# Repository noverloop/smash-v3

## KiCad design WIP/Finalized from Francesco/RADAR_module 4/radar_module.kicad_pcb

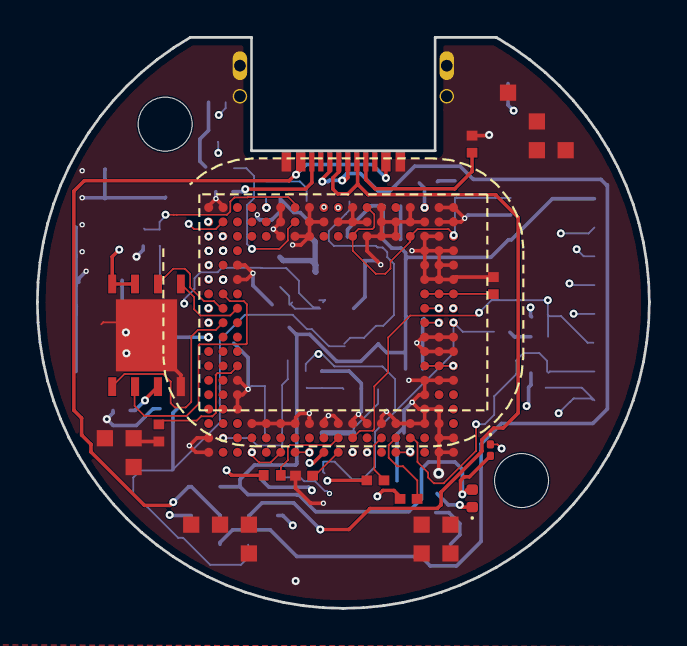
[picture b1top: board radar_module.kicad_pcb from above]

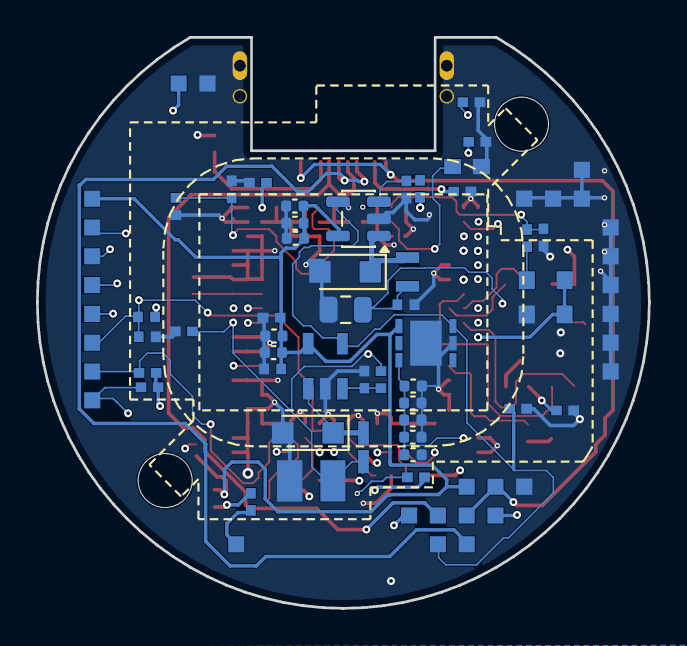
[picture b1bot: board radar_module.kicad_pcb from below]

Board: 20 copper layers, 34.0 x 31.7 mm, 59 parts (46 on the bottom side), 43 nets.

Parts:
C_AWR_1V2_1: T491T 22uF (3528-12 thinnest variant); C_0805_2012Metric
C_AWR_1V2_2, C_AWR_1V3_2, C_AWR_1V8_2, C_AWR_14APLL, C_AWR_14SYNTH: C0402 X7R 100nF; C_0402_1005Metric
C_AWR_1V3_1: T491T 22uF (3528-12 thinnest variant); CP_EIA-3528-12_Kemet-T
C_AWR_1V8_1_1, C_AWR_1V8_1_2, C_AWR_1V8_1_3, C_AWR_1V8_1_4, C_AWR_1V8_1_5: C-Series MIL-PRF-32535 X7R 0603 2.2uF; C_0402_1005Metric
C_AWR_BUCK_IN1_1, C_AWR_BUCK_IN1_2, C_AWR_BUCK_IN1_3, C_AWR_BUCK_IN1_4, C_AWR_BUCK_IN1_5: C-Series MIL-PRF-32535 X7R 0603 2.2uF; C_0402_1005Metric
C_AWR_BUCK_IN2: C0402 X7R 100nF; C_0402_1005Metric
C_AWR_CLKM: SQCSVA 100pF; C_0603_1608Metric
C_AWR_FLASH_VCC: C0402 X7R 100nF; C_0402_1005Metric
C_AWR_NRST: C0402 X7R 100nF; C_0402_1005Metric
C_AWR_OSC_VDD: C0402 X7R 100nF; C_0402_1005Metric
C_AWR_VBGAP: C0402 X7R 100nF; C_0402_1005Metric
C_AWR_VOUT_PA: C0402 X7R 100nF; C_0402_1005Metric
C_NOSE_LED: C0402 X7R 100nF; C_0402_1005Metric
D_AWR_BUCK12, D_AWR_BUCK13: MBRS340T3G; Nexperia_CFP3_SOD-123W
D_NOSE_G: LTST-C190GKT; LED_0402_1005Metric
D_NOSE_R: LTST-C190KRKT; LED_0201_0603Metric
J_USB_C: UJ20-C-H-G-MSMT-1A-P16-TR-67; SAMESKY_UJ20-C-H-G-MSMT-1A-P16-TR-67
J_radar_module_spacer_radar_module_nose_cap: LGA_lands; J_radar_module_spacer_radar_module_nose_cap
L_AWR_BUCK12, L_AWR_BUCK13: TMS201210ALM-2R2MTAA; L_2012_2.0x1.25mm
P_radar_module_spacer_companion_compute_radar_module: LGA_lands; P_radar_module_spacer_companion_compute_radar_module
R_AWR12_FB1, R_AWR12_FB2, R_AWR13_FB2: CRCW0402 100k 1% e3; R_0402_1005Metric
R_AWR13_FB1: CRCW0402 118k 1% e3; R_0402_1005Metric
R_AWR_CLK_SER: CRCW0402 330 1% e3; R_0402_1005Metric
R_AWR_CLK_SH: CRCW0402 390 1% e3; R_0402_1005Metric
R_AWR_DRDY_PU: CRCW0402 10k 1% e3; R_0402_1005Metric
R_AWR_FAULT_PU: CRCW0402 100k 1% e3; R_0402_1005Metric
R_AWR_NERRIN_PU: CRCW0402 10k 1% e3; R_0402_1005Metric
R_AWR_NRST: CRCW0402 10k 1% e3; R_0402_1005Metric
R_AWR_SOP0, R_AWR_SOP1, R_AWR_SOP2: CRCW0402 10k 1% e3; R_0402_1005Metric
R_AWR_WARMRST_PU: CRCW0402 10k 1% e3; R_0402_1005Metric
R_NOSE_LED_G: CRCW0402 330 1% e3; R_0402_1005Metric
R_NOSE_LED_R: CRCW0402 330 1% e3; R_0402_1005Metric
R_RADAR_EN_PD: CRCW0402 100k 1% e3; R_0402_1005Metric
R_USB_CC1, R_USB_CC2: CRCW0402 5.1k 1% e3; R_0402_1005Metric
U_AWR: AWR1843ARBGALPQ1; BGA180C80P18X18_1500X1500X96
U_AWR_BUCK12: LMR10510XMFE/NOPB; SOT-23-5
U_AWR_BUCK13: LMR10510XMFE/NOPB; SOT95P280X145-5N
U_AWR_FLASH: SST26VF080A-104I/MF; SON127P600X500X80-9N-D
U_AWR_LDO18: LDL112PV18R; SON95P300X300X100-7N-D
Y_AWR_HSE: DSC1001CI5-040.0000; DSC1001CI50080000

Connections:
AWR_1V2: C_AWR_1V2_1.1, C_AWR_1V2_2.1, L_AWR_BUCK12.2, R_AWR12_FB1.1, U_AWR.A5, U_AWR.C1, U_AWR.E1, U_AWR.J1, U_AWR.V4, U_AWR.V6, U_AWR.V7, U_AWR.V8, U_AWR.V12, U_AWR.V14, U_AWR.V15
AWR_1V2_FB: R_AWR12_FB1.2, R_AWR12_FB2.1, U_AWR_BUCK12.3
AWR_1V2_SW: D_AWR_BUCK12.1, L_AWR_BUCK12.1, U_AWR_BUCK12.1
AWR_1V3: C_AWR_1V3_1.1, C_AWR_1V3_2.1, L_AWR_BUCK13.2, R_AWR13_FB1.1, U_AWR.H16, U_AWR.H17, U_AWR.H18, U_AWR.J16, U_AWR.J17, U_AWR.J18
AWR_1V3_FB: R_AWR13_FB1.2, R_AWR13_FB2.1, U_AWR_BUCK13.3
AWR_1V3_SW: D_AWR_BUCK13.1, L_AWR_BUCK13.1, U_AWR_BUCK13.1
AWR_1V8: C_AWR_1V8_1_1.1, C_AWR_1V8_1_2.1, C_AWR_1V8_1_3.1, C_AWR_1V8_1_4.1, C_AWR_1V8_1_5.1, C_AWR_1V8_2.1, C_AWR_OSC_VDD.1, U_AWR.A12, U_AWR.B1, U_AWR.C11, U_AWR.C15, U_AWR.C18, U_AWR.F1, U_AWR.K1, U_AWR.M16, U_AWR.M17, U_AWR.M18, U_AWR.U2, U_AWR.V11, U_AWR_LDO18.4, Y_AWR_HSE.1, Y_AWR_HSE.4
AWR_CLKM: C_AWR_CLKM.1, U_AWR.B7
AWR_CLKREF: R_AWR_CLK_SER.2, R_AWR_CLK_SH.1, U_AWR.A7
AWR_DRDY: P_radar_module_spacer_companion_compute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.1, R_AWR_DRDY_PU.2, U_AWR.B2
AWR_FAULT: P_radar_module_spacer_companion_compute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.2, R_AWR_FAULT_PU.2, U_AWR.U15
AWR_NERR_IN: R_AWR_NERRIN_PU.2, U_AWR.U14
AWR_NRESET: C_AWR_NRST.1, P_radar_module_spacer_companion_compute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.3, R_AWR_NRST.2, U_AWR.U11
AWR_OSC_OUT: R_AWR_CLK_SER.1, Y_AWR_HSE.3
AWR_QSPI_CLK: U_AWR.H2, U_AWR_FLASH.6
AWR_QSPI_CS: U_AWR.J2, U_AWR_FLASH.1
AWR_QSPI_SI: U_AWR.H3, U_AWR_FLASH.5
AWR_QSPI_SO: U_AWR.G2, U_AWR_FLASH.2
AWR_SOP0: R_AWR_SOP0.2, U_AWR.U10
AWR_SOP1: R_AWR_SOP1.1, U_AWR.M3
AWR_SOP2: R_AWR_SOP2.1, U_AWR.V10
AWR_SPI_CLK: P_radar_module_spacer_companion_compute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.4, U_AWR.D2
AWR_SPI_CS: P_radar_module_spacer_companion_compute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.5, U_AWR.C2
AWR_SPI_MISO: P_radar_module_spacer_companion_compute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.6, U_AWR.D1
AWR_SPI_MOSI: P_radar_module_spacer_companion_compute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.7, U_AWR.F2
AWR_VOUT_14APLL: C_AWR_14APLL.1, U_AWR.A10
AWR_VOUT_14SYNTH: C_AWR_14SYNTH.1, U_AWR.A9
AWR_VOUT_PA: C_AWR_VOUT_PA.1, U_AWR.G16, U_AWR.G17, U_AWR.G18
AWR_WARM_RST: R_AWR_WARMRST_PU.2, U_AWR.U13
BAT_PROT: C_AWR_BUCK_IN1_1.1, C_AWR_BUCK_IN1_2.1, C_AWR_BUCK_IN1_3.1, C_AWR_BUCK_IN1_4.1, C_AWR_BUCK_IN1_5.1, C_AWR_BUCK_IN2.1, C_NOSE_LED.1, D_NOSE_G.2, D_NOSE_R.2, P_radar_module_spacer_companion_compute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.8, P_radar_module_spacer_companion_compute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.17, U_AWR_BUCK12.5, U_AWR_BUCK13.5, U_AWR_LDO18.6
COMP_3V3: C_AWR_FLASH_VCC.1, P_radar_module_spacer_companion_compute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.9, P_radar_module_spacer_companion_compute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.18, R_AWR_DRDY_PU.1, R_AWR_FAULT_PU.1, R_AWR_NERRIN_PU.1, R_AWR_NRST.1, R_AWR_SOP0.1, R_AWR_WARMRST_PU.1, U_AWR.H1, U_AWR.V9, U_AWR_FLASH.3, U_AWR_FLASH.7, U_AWR_FLASH.8
FLEX_GND: C_AWR_1V2_1.2, C_AWR_1V2_2.2, C_AWR_1V3_1.2, C_AWR_1V3_2.2, C_AWR_1V8_1_1.2, C_AWR_1V8_1_2.2, C_AWR_1V8_1_3.2, C_AWR_1V8_1_4.2, C_AWR_1V8_1_5.2, C_AWR_1V8_2.2, C_AWR_14APLL.2, C_AWR_14SYNTH.2, C_AWR_BUCK_IN1_1.2, C_AWR_BUCK_IN1_2.2, C_AWR_BUCK_IN1_3.2, C_AWR_BUCK_IN1_4.2, C_AWR_BUCK_IN1_5.2, C_AWR_BUCK_IN2.2, C_AWR_CLKM.2, C_AWR_FLASH_VCC.2, C_AWR_NRST.2, C_AWR_OSC_VDD.2, C_AWR_VBGAP.2, C_AWR_VOUT_PA.2, C_NOSE_LED.2, D_AWR_BUCK12.2, D_AWR_BUCK13.2, J_USB_C.A1_B12, J_USB_C.B1_A12, J_USB_C.SH1, J_USB_C.SH2, J_USB_C.SH3, J_USB_C.SH4, J_radar_module_spacer_radar_module_nose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.1, J_radar_module_spacer_radar_module_nose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.2, J_radar_module_spacer_radar_module_nose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.3, J_radar_module_spacer_radar_module_nose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.4, J_radar_module_spacer_radar_module_nose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.5, J_radar_module_spacer_radar_module_nose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.6, J_radar_module_spacer_radar_module_nose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.7, J_radar_module_spacer_radar_module_nose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.8, J_radar_module_spacer_radar_module_nose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.9, J_radar_module_spacer_radar_module_nose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.10, J_radar_module_spacer_radar_module_nose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.11, J_radar_module_spacer_radar_module_nose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.12, J_radar_module_spacer_radar_module_nose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.13, J_radar_module_spacer_radar_module_nose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.14, J_radar_module_spacer_radar_module_nose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.15, P_radar_module_spacer_companion_compute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.10, P_radar_module_spacer_companion_compute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.20, P_radar_module_spacer_companion_compute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.21, P_radar_module_spacer_companion_compute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.22, P_radar_module_spacer_companion_compute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.23, P_radar_module_spacer_companion_compute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.24, P_radar_module_spacer_companion_compute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.25, P_radar_module_spacer_companion_compute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.26, P_radar_module_spacer_companion_compute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.27, P_radar_module_spacer_companion_compute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.28, P_radar_module_spacer_companion_compute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.29, P_radar_module_spacer_companion_compute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.30, R_AWR12_FB2.2, R_AWR13_FB2.2, R_AWR_CLK_SH.2, R_AWR_SOP1.2, R_AWR_SOP2.2, R_RADAR_EN_PD.2, R_USB_CC1.2, R_USB_CC2.2, U_AWR.A1, U_AWR.A2, U_AWR.A6, U_AWR.A8, U_AWR.A11, U_AWR.A13, U_AWR.A15, U_AWR.A17, U_AWR.A18, U_AWR.B6, U_AWR.B8, U_AWR.B9, U_AWR.B10, U_AWR.B11, U_AWR.B12, U_AWR.B13, U_AWR.B14, U_AWR.B15, U_AWR.B16, U_AWR.B17, U_AWR.B18, U_AWR.C6, U_AWR.C7, U_AWR.C8, U_AWR.C12, U_AWR.C13, U_AWR.C14, U_AWR.C16, U_AWR.C17, U_AWR.D16, U_AWR.D17, U_AWR.D18, U_AWR.E3, U_AWR.E16, U_AWR.E17, U_AWR.E18, U_AWR.F3, U_AWR.F16, U_AWR.F17, U_AWR.F18, U_AWR.K16, U_AWR.K17, U_AWR.K18, U_AWR.L16, U_AWR.L17, U_AWR.L18, U_AWR.N3, U_AWR.N16, U_AWR.N17, U_AWR.N18, U_AWR.P3, U_AWR.P16, U_AWR.R3, U_AWR.R16, U_AWR.R17, U_AWR.T4, U_AWR.T5, U_AWR.T6, U_AWR.T7, U_AWR.T8, U_AWR.T9, U_AWR.T10, U_AWR.T11, U_AWR.T12, U_AWR.T13, U_AWR.T14, U_AWR.T15, U_AWR.T16, U_AWR.T17, U_AWR.U1, U_AWR.U17, U_AWR.U18, U_AWR.V1, U_AWR.V17, U_AWR.V18, U_AWR_BUCK12.2, U_AWR_BUCK13.2, U_AWR_FLASH.4, U_AWR_FLASH.9, U_AWR_LDO18.2, U_AWR_LDO18.7, Y_AWR_HSE.2
NOSE_LED_G: P_radar_module_spacer_companion_compute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.11, R_NOSE_LED_G.2
NOSE_LED_G_K: D_NOSE_G.1, R_NOSE_LED_G.1
NOSE_LED_R: P_radar_module_spacer_companion_compute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.12, R_NOSE_LED_R.2
NOSE_LED_R_K: D_NOSE_R.1, R_NOSE_LED_R.1
RADAR_EN: P_radar_module_spacer_companion_compute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.13, R_RADAR_EN_PD.1, U_AWR_BUCK12.4, U_AWR_BUCK13.4, U_AWR_LDO18.1
USB_CC1: J_USB_C.A5, R_USB_CC1.1
USB_CC2: J_USB_C.B5, R_USB_CC2.1
USB_DM: J_USB_C.A7, J_USB_C.B7, P_radar_module_spacer_companion_compute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.14
USB_DP: J_USB_C.A6, J_USB_C.B6, P_radar_module_spacer_companion_compute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.15
USB_VBUS: J_USB_C.A4_B9, J_USB_C.B4_A9, P_radar_module_spacer_companion_compute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.16, P_radar_module_spacer_companion_compute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.19
VBGAP: C_AWR_VBGAP.1, U_AWR.A16

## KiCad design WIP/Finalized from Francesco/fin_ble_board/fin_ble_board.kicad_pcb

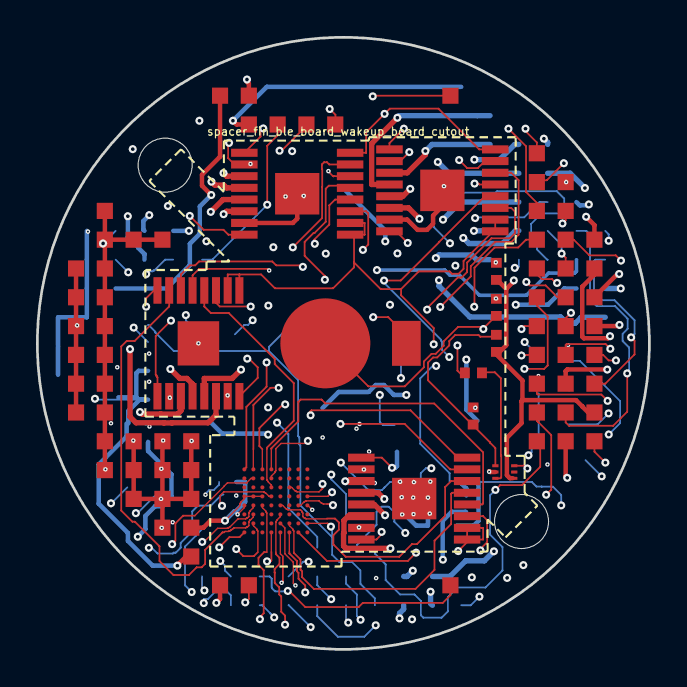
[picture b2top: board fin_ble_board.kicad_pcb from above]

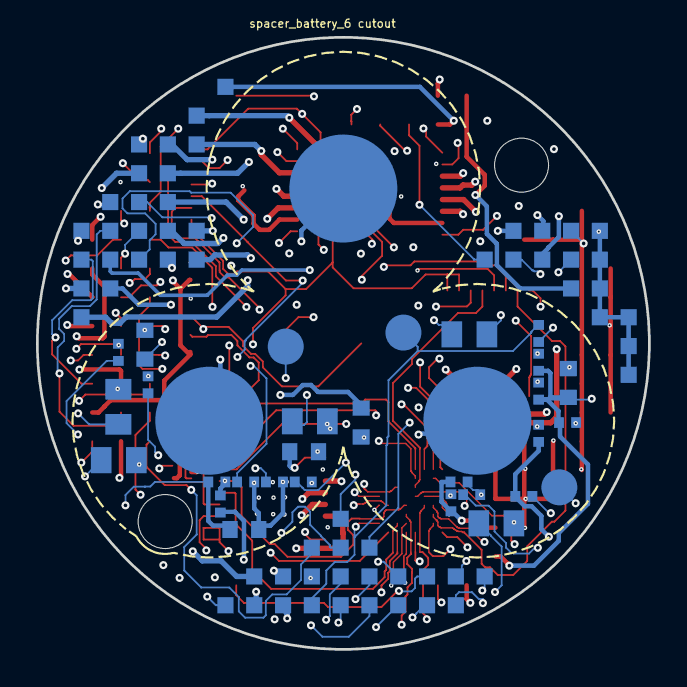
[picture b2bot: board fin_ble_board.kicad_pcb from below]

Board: 14 copper layers, 34.0 x 34.0 mm, 44 parts (31 on the bottom side), 81 nets.

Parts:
C_COMP_PZ: C0402 X7R 100nF; Capacitor_SMD_C_0402_1005Metric
C_FIN1_DVDD, C_FIN2_DVDD, C_FIN3_DVDD, C_FIN4_DVDD: C-Series MIL-PRF-32535 X7R 0805 1uF; Capacitor_SMD_C_0805_2012Metric
C_FIN1_VM, C_FIN2_VM, C_FIN3_VM, C_FIN4_VM: C0402 X7R 100nF; Capacitor_SMD_C_0402_1005Metric
C_FIN_VM_BULK_1, C_FIN_VM_BULK_2, C_FIN_VM_BULK_3, C_FIN_VM_BULK_4, C_FIN_VM_BULK_5: C-Series MIL-PRF-32535 X7R 0603 2.2uF; Capacitor_SMD_C_0603_1608Metric
C_FIN_VREF: C0402 X7R 100nF; Capacitor_SMD_C_0402_1005Metric
C_G0B1_FIN_BULK: C-Series MIL-PRF-32535 X7R 0805 1uF; Capacitor_SMD_C_0805_2012Metric
C_G0B1_FIN_NRST, C_G0B1_FIN_VDD1, C_G0B1_FIN_VDD2, C_G0B1_FIN_VREF: C0402 X7R 100nF; Capacitor_SMD_C_0402_1005Metric
C_J_HALL_FIN_VCC: C0402 X7R 100nF; Capacitor_SMD_C_0402_1005Metric
J_HALL_FIN_GND: J_HALL_FIN_GND; Pogo_Pad_D2.0mm
J_HALL_FIN_OUT: J_HALL_FIN_OUT; Pogo_Pad_D2.0mm
J_HALL_FIN_VCC: J_HALL_FIN_VCC; Pogo_Pad_D2.0mm
J_fin_ble_board_spacer_fin_ble_board_wakeup_board: LGA_lands; J_fin_ble_board_spacer_fin_ble_board_wakeup_board
P_CELL_CONTACTS: BatteryContacts_3
P_PIEZO: SMD10T04R111; PiezoDisc_SMD10T04R111
P_fin_ble_board_spacer_battery_6: LGA_lands; P_fin_ble_board_spacer_battery_6
R_COMP_SER: CRCW0402 100k 1% e3; Resistor_SMD_R_0402_1005Metric
R_FIN1_DECAY, R_FIN2_DECAY, R_FIN3_DECAY, R_FIN4_DECAY: CRCW0402 44.2k 1% e3; Resistor_SMD_R_0402_1005Metric
R_G0B1_FIN_NRST: CRCW0402 10k 1% e3; Resistor_SMD_R_0402_1005Metric
R_J_HALL_FIN_PU: CRCW0402 10k 1% e3; Resistor_SMD_R_0402_1005Metric
R_PIEZO_BLEED: CRCW0402 1M 1% e3; Resistor_SMD_R_0402_1005Metric
R_THR1: CRCW0402 1M 1% e3; Resistor_SMD_R_0402_1005Metric
R_THR2: CRCW0402 100k 1% e3; Resistor_SMD_R_0402_1005Metric
U_COMP_PZ: TLV3691IDPFR; DPF0006A
U_FIN1, U_FIN2, U_FIN3, U_FIN4: DRV8428EPWPR; SOP65P640X120-17N
U_G0B1_FIN: STM32G0B1REI6N; BGA64C50P8X8_500X500X60

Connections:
3V3: C_G0B1_FIN_BULK.1, C_G0B1_FIN_VDD1.1, C_G0B1_FIN_VDD2.1, C_G0B1_FIN_VREF.1, C_J_HALL_FIN_VCC.1, J_HALL_FIN_VCC.1, J_fin_ble_board_spacer_fin_ble_board_wa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.1, J_fin_ble_board_spacer_fin_ble_board_wa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.35, J_fin_ble_board_spacer_fin_ble_board_wa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.41, P_fin_ble_board_spacer_battery_6.23, P_fin_ble_board_spacer_battery_6.47, P_fin_ble_board_spacer_battery_6.52, R_G0B1_FIN_NRST.1, R_J_HALL_FIN_PU.1, U_G0B1_FIN.D1, U_G0B1_FIN.D2, U_G0B1_FIN.D3, U_G0B1_FIN.D8
3V3_AON: C_COMP_PZ.1, J_fin_ble_board_spacer_fin_ble_board_wa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.2, J_fin_ble_board_spacer_fin_ble_board_wa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.36, P_fin_ble_board_spacer_battery_6.24, P_fin_ble_board_spacer_battery_6.48, R_THR1.1, U_COMP_PZ.6
ACTIVATE_CONFIRM: J_fin_ble_board_spacer_fin_ble_board_wa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.3, P_fin_ble_board_spacer_battery_6.3
ACTIVATE_SET: J_fin_ble_board_spacer_fin_ble_board_wa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.4, P_fin_ble_board_spacer_battery_6.4
BAT_CELL1_POS: J_fin_ble_board_spacer_fin_ble_board_wa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.5, P_CELL_CONTACTS.1
BAT_CELL2_POS: J_fin_ble_board_spacer_fin_ble_board_wa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.6, P_CELL_CONTACTS.2
BAT_CELL3_POS: J_fin_ble_board_spacer_fin_ble_board_wa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.7, P_CELL_CONTACTS.3
BAT_PROT: J_fin_ble_board_spacer_fin_ble_board_wa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.8, J_fin_ble_board_spacer_fin_ble_board_wa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.37, P_fin_ble_board_spacer_battery_6.5, P_fin_ble_board_spacer_battery_6.49
BAT_RAW: J_fin_ble_board_spacer_fin_ble_board_wa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.9, J_fin_ble_board_spacer_fin_ble_board_wa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.38, P_fin_ble_board_spacer_battery_6.6, P_fin_ble_board_spacer_battery_6.50
BOOT0: J_fin_ble_board_spacer_fin_ble_board_wa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.10, P_fin_ble_board_spacer_battery_6.7
COMP_5V: J_fin_ble_board_spacer_fin_ble_board_wa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.11, J_fin_ble_board_spacer_fin_ble_board_wa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.39, P_fin_ble_board_spacer_battery_6.8, P_fin_ble_board_spacer_battery_6.51
COMP_5V_RAW: C_FIN1_VM.1, C_FIN2_VM.1, C_FIN3_VM.1, C_FIN4_VM.1, C_FIN_VM_BULK_1.1, C_FIN_VM_BULK_2.1, C_FIN_VM_BULK_3.1, C_FIN_VM_BULK_4.1, C_FIN_VM_BULK_5.1, J_fin_ble_board_spacer_fin_ble_board_wa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.12, J_fin_ble_board_spacer_fin_ble_board_wa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.40, U_FIN1.1, U_FIN2.1, U_FIN3.1, U_FIN4.1
COMP_INM: R_THR1.2, R_THR2.1, U_COMP_PZ.3
COMP_INP: R_COMP_SER.2, U_COMP_PZ.1
COMP_OUT: J_fin_ble_board_spacer_fin_ble_board_wa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.13, U_COMP_PZ.4
COMP_SWDCLK: J_fin_ble_board_spacer_fin_ble_board_wa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.14, P_fin_ble_board_spacer_battery_6.9
COMP_SWDIO: J_fin_ble_board_spacer_fin_ble_board_wa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.15, P_fin_ble_board_spacer_battery_6.10
EXT_CAN_RX: J_fin_ble_board_spacer_fin_ble_board_wa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.16, P_fin_ble_board_spacer_battery_6.11
EXT_CAN_TX: J_fin_ble_board_spacer_fin_ble_board_wa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.17, P_fin_ble_board_spacer_battery_6.14
FIN1_AEN: U_FIN1.15, U_G0B1_FIN.E3
FIN1_AOUT1: P_fin_ble_board_spacer_battery_6.13, U_FIN1.3
FIN1_AOUT2: P_fin_ble_board_spacer_battery_6.12, U_FIN1.4
FIN1_APH: U_FIN1.14, U_G0B1_FIN.H5
FIN1_BEN: U_FIN1.13, U_G0B1_FIN.F5
FIN1_BOUT1: P_fin_ble_board_spacer_battery_6.15, U_FIN1.6
FIN1_BOUT2: P_fin_ble_board_spacer_battery_6.16, U_FIN1.5
FIN1_BPH: U_FIN1.12, U_G0B1_FIN.B4
FIN1_DECAY: R_FIN1_DECAY.1, U_FIN1.11
FIN1_DVDD: C_FIN1_DVDD.1, U_FIN1.8
FIN2_AEN: U_FIN2.15, U_G0B1_FIN.F2
FIN2_AOUT1: P_fin_ble_board_spacer_battery_6.17, U_FIN2.3
FIN2_AOUT2: P_fin_ble_board_spacer_battery_6.18, U_FIN2.4
FIN2_APH: U_FIN2.14, U_G0B1_FIN.H6
FIN2_BEN: U_FIN2.13, U_G0B1_FIN.G5
FIN2_BOUT1: P_fin_ble_board_spacer_battery_6.19, U_FIN2.6
FIN2_BOUT2: P_fin_ble_board_spacer_battery_6.20, U_FIN2.5
FIN2_BPH: U_FIN2.12, U_G0B1_FIN.C4
FIN2_DECAY: R_FIN2_DECAY.1, U_FIN2.11
FIN2_DVDD: C_FIN2_DVDD.1, U_FIN2.8
FIN3_AEN: U_FIN3.15, U_G0B1_FIN.G2
FIN3_AOUT1: P_fin_ble_board_spacer_battery_6.21, U_FIN3.3
FIN3_AOUT2: P_fin_ble_board_spacer_battery_6.22, U_FIN3.4
FIN3_APH: U_FIN3.14, U_G0B1_FIN.E7
FIN3_BEN: U_FIN3.13, U_G0B1_FIN.H7
FIN3_BOUT1: P_fin_ble_board_spacer_battery_6.1, U_FIN3.6
FIN3_BOUT2: P_fin_ble_board_spacer_battery_6.2, U_FIN3.5
FIN3_BPH: U_FIN3.12, U_G0B1_FIN.D4
FIN3_DECAY: R_FIN3_DECAY.1, U_FIN3.11
FIN3_DVDD: C_FIN3_DVDD.1, U_FIN3.8
FIN4_AEN: U_FIN4.15, U_G0B1_FIN.H1
FIN4_AOUT1: P_fin_ble_board_spacer_battery_6.25, U_FIN4.3
FIN4_AOUT2: P_fin_ble_board_spacer_battery_6.26, U_FIN4.4
FIN4_APH: U_FIN4.14, U_G0B1_FIN.E5
FIN4_BEN: U_FIN4.13, U_G0B1_FIN.G6
FIN4_BOUT1: P_fin_ble_board_spacer_battery_6.27, U_FIN4.6
FIN4_BOUT2: P_fin_ble_board_spacer_battery_6.28, U_FIN4.5
FIN4_BPH: U_FIN4.12, U_G0B1_FIN.A4
FIN4_DECAY: R_FIN4_DECAY.1, U_FIN4.11
FIN4_DVDD: C_FIN4_DVDD.1, U_FIN4.8
FIN_HALL: J_HALL_FIN_OUT.1, P_fin_ble_board_spacer_battery_6.29, R_J_HALL_FIN_PU.2, U_G0B1_FIN.G8
FIN_NSLEEP: U_FIN1.16, U_FIN2.16, U_FIN3.16, U_FIN4.16, U_G0B1_FIN.A3
FIN_VREF: C_FIN_VREF.1, U_FIN1.9, U_FIN1.10, U_FIN2.9, U_FIN2.10, U_FIN3.9, U_FIN3.10, U_FIN4.9, U_FIN4.10, U_G0B1_FIN.H4
FLEX_GND: C_COMP_PZ.2, C_FIN1_DVDD.2, C_FIN1_VM.2, C_FIN2_DVDD.2, C_FIN2_VM.2, C_FIN3_DVDD.2, C_FIN3_VM.2, C_FIN4_DVDD.2, C_FIN4_VM.2, C_FIN_VM_BULK_1.2, C_FIN_VM_BULK_2.2, C_FIN_VM_BULK_3.2, C_FIN_VM_BULK_4.2, C_FIN_VM_BULK_5.2, C_FIN_VREF.2, C_G0B1_FIN_BULK.2, C_G0B1_FIN_NRST.2, C_G0B1_FIN_VDD1.2, C_G0B1_FIN_VDD2.2, C_G0B1_FIN_VREF.2, C_J_HALL_FIN_VCC.2, J_HALL_FIN_GND.1, J_fin_ble_board_spacer_fin_ble_board_wa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.18, J_fin_ble_board_spacer_fin_ble_board_wa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.42, J_fin_ble_board_spacer_fin_ble_board_wa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.43, J_fin_ble_board_spacer_fin_ble_board_wa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.44, J_fin_ble_board_spacer_fin_ble_board_wa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.45, J_fin_ble_board_spacer_fin_ble_board_wa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.46, J_fin_ble_board_spacer_fin_ble_board_wa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.47, J_fin_ble_board_spacer_fin_ble_board_wa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.48, J_fin_ble_board_spacer_fin_ble_board_wa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.49, J_fin_ble_board_spacer_fin_ble_board_wa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.50, J_fin_ble_board_spacer_fin_ble_board_wa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.51, J_fin_ble_board_spacer_fin_ble_board_wa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.52, J_fin_ble_board_spacer_fin_ble_board_wa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.53, J_fin_ble_board_spacer_fin_ble_board_wa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.54, J_fin_ble_board_spacer_fin_ble_board_wa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.55, J_fin_ble_board_spacer_fin_ble_board_wa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.56, J_fin_ble_board_spacer_fin_ble_board_wa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.57, J_fin_ble_board_spacer_fin_ble_board_wa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.58, J_fin_ble_board_spacer_fin_ble_board_wa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.59, J_fin_ble_board_spacer_fin_ble_board_wa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.60, J_fin_ble_board_spacer_fin_ble_board_wa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.61, J_fin_ble_board_spacer_fin_ble_board_wa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.62, J_fin_ble_board_spacer_fin_ble_board_wa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.63, J_fin_ble_board_spacer_fin_ble_board_wa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.64, J_fin_ble_board_spacer_fin_ble_board_wa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.65, J_fin_ble_board_spacer_fin_ble_board_wa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.66, J_fin_ble_board_spacer_fin_ble_board_wa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.67, J_fin_ble_board_spacer_fin_ble_board_wa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.68, J_fin_ble_board_spacer_fin_ble_board_wa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.69, P_PIEZO.2, P_fin_ble_board_spacer_battery_6.30, P_fin_ble_board_spacer_battery_6.53, P_fin_ble_board_spacer_battery_6.54, P_fin_ble_board_spacer_battery_6.55, P_fin_ble_board_spacer_battery_6.56, P_fin_ble_board_spacer_battery_6.57, P_fin_ble_board_spacer_battery_6.58, P_fin_ble_board_spacer_battery_6.59, P_fin_ble_board_spacer_battery_6.60, R_FIN1_DECAY.2, R_FIN2_DECAY.2, R_FIN3_DECAY.2, R_FIN4_DECAY.2, R_PIEZO_BLEED.2, R_THR2.2, U_COMP_PZ.2, U_FIN1.2, U_FIN1.7, U_FIN1.17, U_FIN2.2, U_FIN2.7, U_FIN2.17, U_FIN3.2, U_FIN3.7, U_FIN3.17, U_FIN4.2, U_FIN4.7, U_FIN4.17, U_G0B1_FIN.E1, U_G0B1_FIN.E8
G0B1_FIN_NRST: C_G0B1_FIN_NRST.1, R_G0B1_FIN_NRST.2, U_G0B1_FIN.E2
GPIO_EXT_0: J_fin_ble_board_spacer_fin_ble_board_wa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.19, P_fin_ble_board_spacer_battery_6.31
GPIO_EXT_1: J_fin_ble_board_spacer_fin_ble_board_wa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.20, P_fin_ble_board_spacer_battery_6.32
GPIO_EXT_2: J_fin_ble_board_spacer_fin_ble_board_wa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.21, P_fin_ble_board_spacer_battery_6.33
GPIO_EXT_3: J_fin_ble_board_spacer_fin_ble_board_wa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.22, P_fin_ble_board_spacer_battery_6.34
H3LIS_INT1: J_fin_ble_board_spacer_fin_ble_board_wa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.23, P_fin_ble_board_spacer_battery_6.35
I2C3_SCL: J_fin_ble_board_spacer_fin_ble_board_wa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.24, P_fin_ble_board_spacer_battery_6.36
I2C3_SDA: J_fin_ble_board_spacer_fin_ble_board_wa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.25, P_fin_ble_board_spacer_battery_6.37
JUMP_WAKE: J_fin_ble_board_spacer_fin_ble_board_wa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.26, P_fin_ble_board_spacer_battery_6.38
NRST: J_fin_ble_board_spacer_fin_ble_board_wa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.27, P_fin_ble_board_spacer_battery_6.39
PIEZO_P: P_PIEZO.1, R_COMP_SER.1, R_PIEZO_BLEED.1
SWO: J_fin_ble_board_spacer_fin_ble_board_wa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.28, P_fin_ble_board_spacer_battery_6.40
SYS_I2C_SCL: J_fin_ble_board_spacer_fin_ble_board_wa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.29, P_fin_ble_board_spacer_battery_6.41
SYS_I2C_SDA: J_fin_ble_board_spacer_fin_ble_board_wa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.30, P_fin_ble_board_spacer_battery_6.42
SYS_SPI_CS_FIN: J_fin_ble_board_spacer_fin_ble_board_wa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.31, P_fin_ble_board_spacer_battery_6.43, U_G0B1_FIN.C6
SYS_SPI_MISO: J_fin_ble_board_spacer_fin_ble_board_wa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.32, P_fin_ble_board_spacer_battery_6.44, U_G0B1_FIN.A1
SYS_SPI_MOSI: J_fin_ble_board_spacer_fin_ble_board_wa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.33, P_fin_ble_board_spacer_battery_6.45, U_G0B1_FIN.B2
SYS_SPI_SCLK: J_fin_ble_board_spacer_fin_ble_board_wa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.34, P_fin_ble_board_spacer_battery_6.46, U_G0B1_FIN.A2
